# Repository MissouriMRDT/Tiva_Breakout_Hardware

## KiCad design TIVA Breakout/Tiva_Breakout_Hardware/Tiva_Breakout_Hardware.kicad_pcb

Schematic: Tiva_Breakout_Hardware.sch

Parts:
12V_A1: PH_2x5; JTAG_ARM_Connector_10_Pin
Conn1: Molex_SL_02; MOLEX_SL_02_Horizontal
Conn30V_L1, Conn30V_R1: PH_2x5; JTAG_ARM_Connector_10_Pin
ConnPCH_C2: PH_2x5; JTAG_ARM_Connector_10_Pin
D1: GRN; LED_0603_1608Metric_Pad1.05x0.95mm_HandSolder
D2, D3, D4, D5, D6, D7, D8, D9, D10, D11, D12, D13, D15, D16, D17, D18, D21, D22, D23, D24: BLU; LED_0603_1608Metric_Pad1.05x0.95mm_HandSolder
D25: RED; LED_0603_1608Metric_Pad1.05x0.95mm_HandSolder
R1, R2, R3, R4, R5, R6, R7, R8, R9, R10, R11, R12, R13, R15, R16, R17, R18, R21, R22, R23, R24, R25: 330; R_0603_1608Metric_Pad1.05x0.95mm_HandSolder
R19, R20, R26, R27, R28, R29, R30, R31: 10k; R_0603_1608Metric_Pad1.05x0.95mm_HandSolder
U1: TM4C129E_Launchpad; Tiva_Breakout

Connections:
12V_EN: Conn30V_R1.2, R9.2, U1.PA4 (B2_9)
12V_ISENSE: Conn30V_R1.4, U1.PK2 (B2_7)
+3V3: Conn1.2, R1.2, U1.+3V3 (A1_1), U1.+3V3' (A2_1)
ACT_EN: 12V_A1.8, R12.2, U1.PL0 (C1_7)
ACT_ISENSE: 12V_A1.2, U1.PD1 (D1_6)
AUX_EN: Conn30V_R1.6, R8.2, U1.PQ0 (A2_7)
AUX_ISENSE: Conn30V_R1.8, U1.PK1 (B2_6)
ERROR: R25.2, U1.PB2 (A1_9)
GND: 12V_A1.1, 12V_A1.3, 12V_A1.5, 12V_A1.7, 12V_A1.9, Conn1.1, ConnPCH_C2.9, ConnPCH_C2.10, D1.1, D2.1, D3.1, D4.1, D5.1, D6.1, D7.1, D8.1, D9.1, D10.1, D11.1, D12.1, D13.1, D15.1, D16.1, D17.1, D18.1, D21.1, D22.1, D23.1, D24.1, D25.1, R19.1, R20.1, R26.1, R27.1, R28.1, R29.1, R30.1, R31.1, U1.GND (B1_2)
LOG_EN: 12V_A1.6, R13.2, U1.PL5 (C1_6)
LOG_ISENSE: 12V_A1.10, U1.PD0 (D1_7)
M1_EN: Conn30V_L1.1, R2.2, U1.PP1 (A2_4)
M1_ISENSE: Conn30V_L1.2, U1.PD4 (A2_5)
M2_EN: Conn30V_L1.4, R3.2, U1.PN4 (A2_10)
M2_ISENSE: Conn30V_L1.6, U1.PD5 (A2_6)
M3_EN: Conn30V_L1.8, R4.2, U1.PP4 (A2_8)
M3_ISENSE: Conn30V_L1.10, U1.PK3 (B2_8)
M4_EN: Conn30V_L1.9, R5.2, U1.PN5 (A2_9)
M4_ISENSE: Conn30V_L1.7, U1.PD2 (A2_2)
M5_EN: Conn30V_L1.5, R6.2, U1.PA5 (B2_10)
M5_ISENSE: Conn30V_L1.3, U1.PB4 (B2_3)
M6_EN: Conn30V_R1.7, R11.2, U1.PP0 (A2_3)
M6_ISENSE: Conn30V_R1.5, U1.PE5 (A1_6)
unnamed: D1.2, R1.1
unnamed: D2.2, R2.1
unnamed: D3.2, R3.1
unnamed: D4.2, R4.1
unnamed: D5.2, R5.1
unnamed: D6.2, R6.1
unnamed: D7.2, R7.1
unnamed: D8.2, R8.1
unnamed: D9.2, R9.1
unnamed: D10.2, R10.1
unnamed: D11.2, R11.1
unnamed: D12.2, R12.1
unnamed: D13.2, R13.1
unnamed: D15.2, R15.1
unnamed: D16.2, R16.1
unnamed: D17.2, R17.1
unnamed: D18.2, R18.1
unnamed: D21.2, R21.1
unnamed: D22.2, R22.1
unnamed: D23.2, R23.1
unnamed: D24.2, R24.1
unnamed: D25.2, R25.1
PB1_EN: ConnPCH_C2.1, R19.2, R24.2, U1.PC6 (A1_5)
PB2_EN: ConnPCH_C2.2, R18.2, R28.2, U1.PE3 (B1_6)
PB3_EN: ConnPCH_C2.3, R20.2, R23.2, U1.PC5 (A1_4)
PB4_EN: ConnPCH_C2.4, R17.2, R29.2, U1.PE2 (B1_5)
PB5_EN: ConnPCH_C2.5, R22.2, R26.2, U1.PC4 (A1_3)
PB6_EN: ConnPCH_C2.6, R16.2, R30.2, U1.PE1 (B1_4)
PB7_EN: ConnPCH_C2.7, R21.2, R27.2, U1.PE4 (A1_2)
PB8_EN: ConnPCH_C2.8, R15.2, R31.2, U1.PE0 (B1_3)
RKT_EN: Conn30V_R1.10, R7.2, U1.PK0 (B2_5)
RKT_ISENSE: Conn30V_R1.9, U1.PB5 (B2_4)
SP_EN: Conn30V_R1.3, R10.2, U1.PB3 (A1_10)
SP_ISENSE: Conn30V_R1.1, U1.PD3 (A1_7)

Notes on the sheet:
CONNECTORS
30V_R
30V_L
12V
30V LED
12V LED
Power Input
PATCH PANEL LED/PULLDOWN
3V3_LED
ERROR_LED
PATCH
30V
ERROR

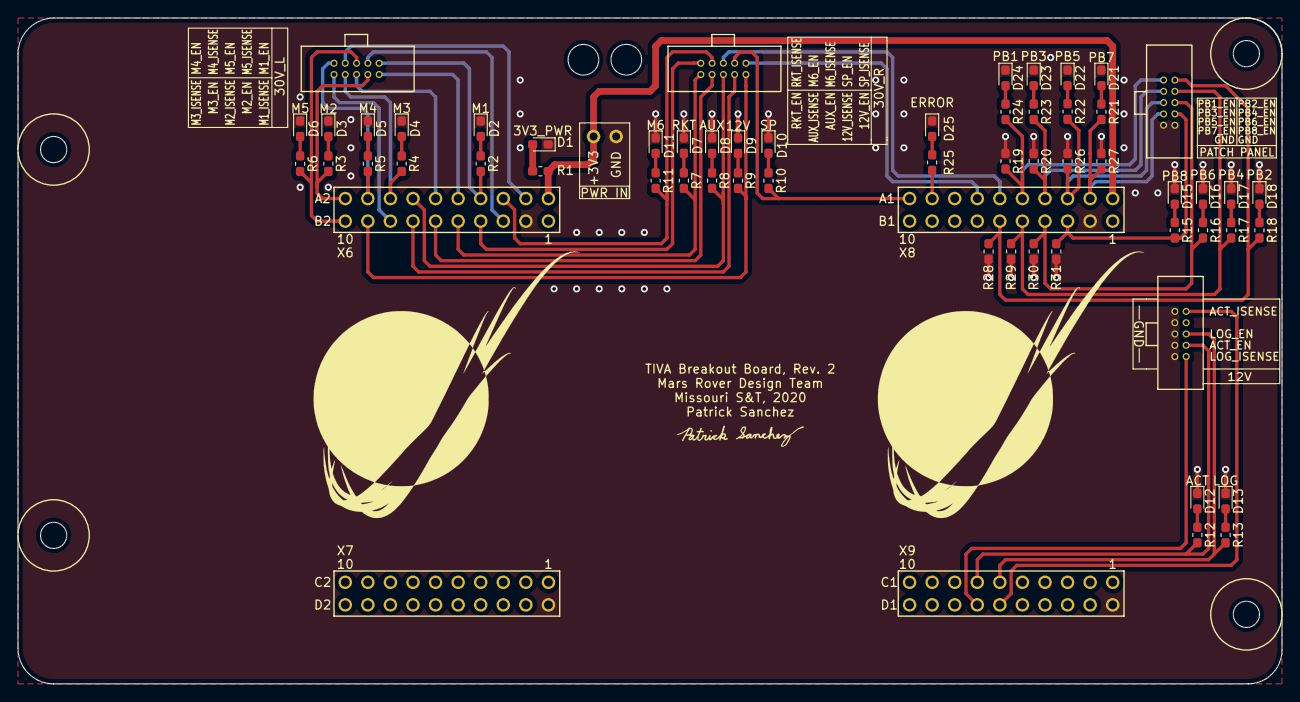
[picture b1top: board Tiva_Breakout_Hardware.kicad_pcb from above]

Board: 2 copper layers, 142.2 x 74.9 mm, 58 parts (1 on the bottom side), 57 nets.

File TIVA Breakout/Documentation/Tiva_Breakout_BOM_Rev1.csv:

Id,Designator,Package,Quantity,Designation,Item Name,Part Number,Vendor,Cost per (100+),Cost,URL
1,"R25,R7,R1,R2,R3,R4,R5,R6,R8,R9,R10,R11,R12,R13,R14,R15,R16,R17,R18,R21,R22,R23,R24",R_0603_1608Metric_Pad1.05x0.95mm_HandSolder,22,330,RES SMD 10k 1% 0603,65T8183,Newark,0.023,,https://www.newark.com/bourns/cr0603-jw-331glf/res-thick-fil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
2,D25,LED_0603_1608Metric_Pad1.05x0.95mm_HandSolder,1,RED,LED RED 20mA 2V 0603,09J9435,Newark,0.309,,https://www.newark.com/lumex/sml-lx0603siw-tr/led-red-0-8mm-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
5,U1,Tiva_Breakout,1,TM4C129E_Launchpad,CONN HDR 20POS .1 GOLD PCB,72K2943,Newark,2.54,,https://www.newark.com/amphenol-icc-fci/66953-010lf/board-bo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
,U1,Tiva_Breakout,1,TM4C129E_Launchpad,EVAL BOARD FOR TM4C129E,28AH2566,Newark,27.97,,https://www.newark.com/texas-instruments/ek-tm4c129exl/evalu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
8,D1,LED_0603_1608Metric_Pad1.05x0.95mm_HandSolder,1,GRN,LED GREEN 20mA 2.2V 0603,75K1440,Newark,0.091,,"https://www.newark.com/lumex/sml-lx0603gw-tr/led-green-0-8mm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,%20QuasarBrite,%20Green,%20SMD,%200603,%2020%20mA,%202%20V"
9,Conn1,MOLEX_SL_02_Horizontal,1,Molex_SL_02,"SL 2 Contacts, Header, THT",59H2645,Newark,0.568,,https://www.newark.com/molex/70543-0001/connector-header-2po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
10,"12V_A1,Conn30V_L1,Conn30V_R1,ConnPCH_C2",PinHeader_2x05_P1.27mm_Vertical,4,PH_2x5,"Connector Header Through Hole 10 position 0.050"" (1.27mm)",1175-1627-ND,Digikey,0.414,,https://www.digikey.com/product-detail/en/cnc-tech/3220-10-0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
11,"D2,D3,D4,D5,D6,D7,D8,D9,D10,D11,D12,D13,D14,D15,D16,D17,D18,D21,D22,D23,D24",LED_0603_1608Metric_Pad1.05x0.95mm_HandSolder,20,BLU,LED BLUE 20mA 3.5V 0603,70M9169,Newark,0.939,,"https://www.newark.com/lumex/sml-lx0603usbw-tr/led-blue-0-8m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,%20%20Blue,%20SMD,%200603,%2020%20mA,%203.5%20V"
12,"R19,R20,R26,R27,R28,R29,R30,R31",R_0603_1608Metric_Pad1.05x0.95mm_HandSolder,8,10k,RES SMD 10k 1% 0603,59AC6935,Newark,0.037,,https://www.newark.com/rohm/esr03ezpf1002/res-10k-1-0603-thi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

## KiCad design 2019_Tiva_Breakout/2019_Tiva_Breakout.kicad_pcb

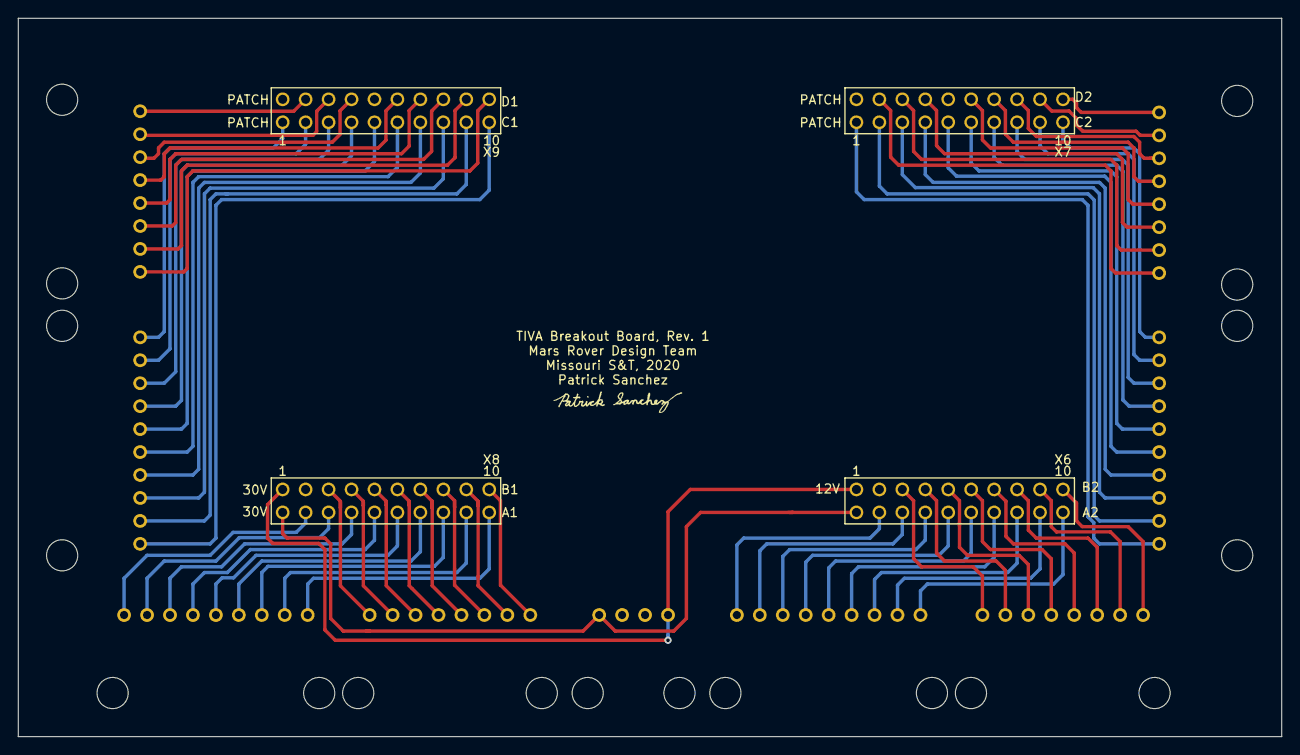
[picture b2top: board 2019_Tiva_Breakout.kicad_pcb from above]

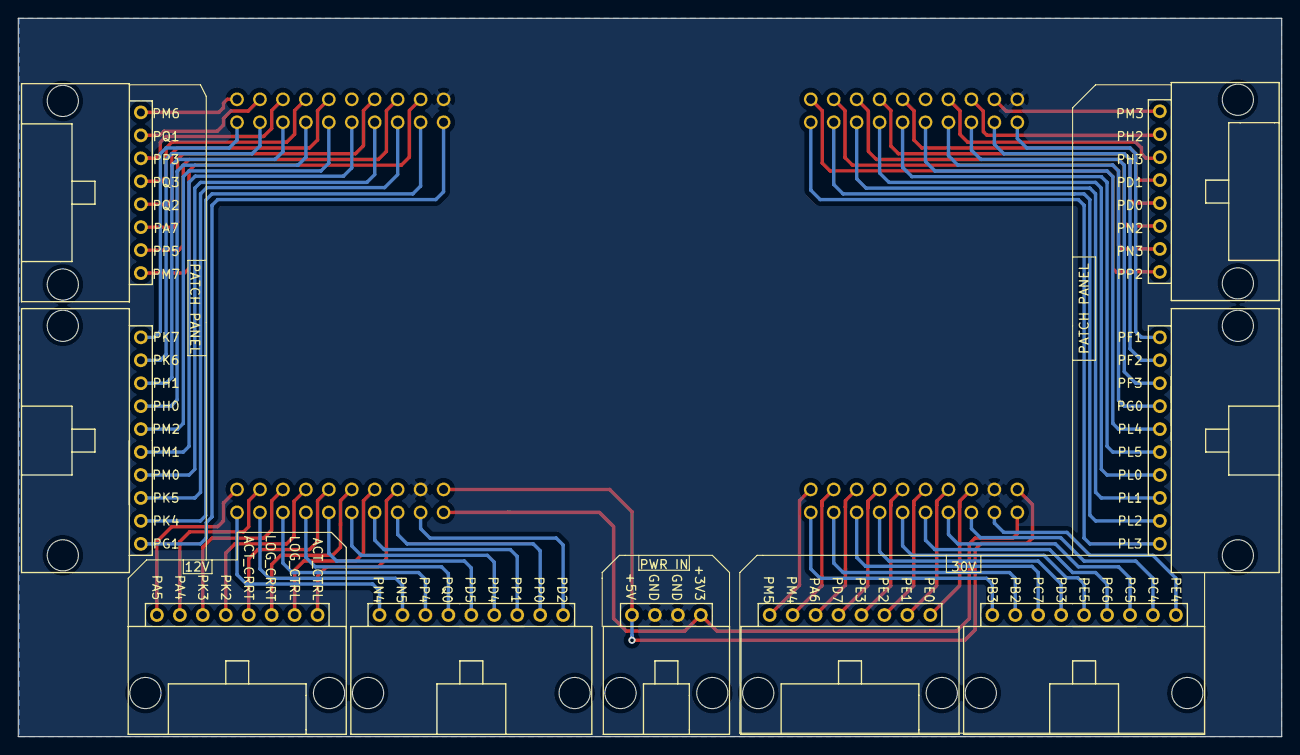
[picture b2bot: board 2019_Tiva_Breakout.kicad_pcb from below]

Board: 2 copper layers, 139.8 x 79.5 mm, 10 parts (9 on the bottom side), 73 nets.

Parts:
ConnA1, ConnA2: Molex_SL_09; MOLEX_SL_09_Horizontal
ConnB1, ConnB2: Molex_SL_08; MOLEX_SL_08_Horizontal
ConnC1, ConnC2: Molex_SL_10; MOLEX_SL_10_Horizontal
ConnD1, ConnD2: Molex_SL_08; MOLEX_SL_08_Horizontal
ConnIN1: Molex_SL_04; MOLEX_SL_04_Horizontal
U1: TM4C129E_Launchpad; Tiva_Breakout

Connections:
+3V3: ConnIN1.1, U1.+3V3, U1.+3V3'
+5VA: ConnIN1.4, U1.+5V, U1.+5V'
GND: ConnIN1.2, ConnIN1.3, U1.GND
unnamed: ConnA1.1, U1.PE4
unnamed: ConnA1.2, U1.PC4
unnamed: ConnA1.3, U1.PC5
unnamed: ConnA1.4, U1.PC6
unnamed: ConnA1.5, U1.PE5
unnamed: ConnA1.6, U1.PD3
unnamed: ConnA1.7, U1.PC7
unnamed: ConnA1.8, U1.PB2
unnamed: ConnA1.9, U1.PB3
unnamed: ConnA2.1, U1.PD2
unnamed: ConnA2.2, U1.PP0
unnamed: ConnA2.3, U1.PP1
unnamed: ConnA2.4, U1.PD4
unnamed: ConnA2.5, U1.PD5
unnamed: ConnA2.6, U1.PQ0
unnamed: ConnA2.7, U1.PP4
unnamed: ConnA2.8, U1.PN5
unnamed: ConnA2.9, U1.PN4
unnamed: ConnB1.1, U1.PE0
unnamed: ConnB1.2, U1.PE1
unnamed: ConnB1.3, U1.PE2
unnamed: ConnB1.4, U1.PE3
unnamed: ConnB1.5, U1.PD7
unnamed: ConnB1.6, U1.PA6
unnamed: ConnB1.7, U1.PM4
unnamed: ConnB1.8, U1.PM5
unnamed: ConnB2.1, U1.PB4
unnamed: ConnB2.2, U1.PB5
unnamed: ConnB2.3, U1.PK0
unnamed: ConnB2.4, U1.PK1
unnamed: ConnB2.5, U1.PK2
unnamed: ConnB2.6, U1.PK3
unnamed: ConnB2.7, U1.PA4
unnamed: ConnB2.8, U1.PA5
unnamed: ConnC1.1, U1.PF1
unnamed: ConnC1.2, U1.PF2
unnamed: ConnC1.3, U1.PF3
unnamed: ConnC1.4, U1.PG0
unnamed: ConnC1.5, U1.PL4
unnamed: ConnC1.6, U1.PL5
unnamed: ConnC1.7, U1.PL0
unnamed: ConnC1.8, U1.PL1
unnamed: ConnC1.9, U1.PL2
unnamed: ConnC1.10, U1.PL3
unnamed: ConnC2.1, U1.PG1
unnamed: ConnC2.2, U1.PK4
unnamed: ConnC2.3, U1.PK5
unnamed: ConnC2.4, U1.PM0
unnamed: ConnC2.5, U1.PM1
unnamed: ConnC2.6, U1.PM2
unnamed: ConnC2.7, U1.PH0
unnamed: ConnC2.8, U1.PH1
unnamed: ConnC2.9, U1.PK6
unnamed: ConnC2.10, U1.PK7
unnamed: ConnD1.1, U1.PM3
unnamed: ConnD1.2, U1.PH2
unnamed: ConnD1.3, U1.PH3
unnamed: ConnD1.4, U1.PD1
unnamed: ConnD1.5, U1.PD0
unnamed: ConnD1.6, U1.PN2
unnamed: ConnD1.7, U1.PN3
unnamed: ConnD1.8, U1.PP2
unnamed: ConnD2.1, U1.PM7
unnamed: ConnD2.2, U1.PP5
unnamed: ConnD2.3, U1.PA7
unnamed: ConnD2.4, U1.PQ2
unnamed: ConnD2.5, U1.PQ3
unnamed: ConnD2.6, U1.PP3
unnamed: ConnD2.7, U1.PQ1
unnamed: ConnD2.8, U1.PM6

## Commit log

2019-10-06 Inital commit
2019-10-09 renamed files to proper tiva spelling
2019-10-09 removed old files
2019-10-09 Updated silkscreen with required information
2019-10-09 Added start of BOM file
2019-10-09 renamed board folder to match standards
2019-10-10 Adjustments to labels for readability
2019-11-03 Removed unnecessary connectors in schematic to reflect other boards
2019-11-14 rearranged pcb to account for physical layout
2019-11-15 In process of changing layout for smaller board
2019-11-16 In process of rearranging for new layout
2019-11-21 New layout, as board is on left of others now. Changed pin assignments.
2019-11-22 Corrected schematic to match 30V board
2019-11-23 Ready for CDR
2019-11-23 CDR Ready 2
2019-12-08 Finished 30V LEDs and connectors
2019-12-09 Rerouted 30V for readability; routed 12V and LEDs
2019-12-09 Finished all wiring and LEDs, need resizing and silkscreen
2019-12-12 Finished layout, minus some silk screen stuff
2019-12-13 Added pulldown resistors & LED colors
2019-12-13 Added pullup resistors and pin labels
2019-12-14 Ready for PRR
2019-12-14 fixed some silkscreen labels
2019-12-14 completely finished PRR and BOM
2019-12-19 Fixed gerbs (no drill files here either)
2020-01-13 Ready for Board Review, questions about PB#
2020-01-21 Created step file
2020-02-12 30V connectors and part of patch panel finished
2020-02-15 Ready for Rev 2 Review
2020-02-15 Github nuked the last one, so lets try again
2020-02-15 Github please stop corrupting my files
2020-02-15 Slight schematic update
2020-02-17 updated gerbs
